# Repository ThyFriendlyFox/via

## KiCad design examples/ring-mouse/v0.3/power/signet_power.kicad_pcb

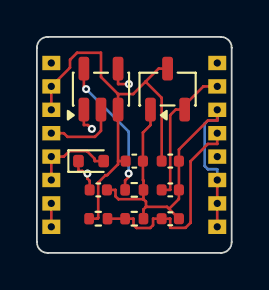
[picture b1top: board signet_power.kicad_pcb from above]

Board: 4 copper layers, 10.8 x 12.0 mm, 13 parts (0 on the bottom side), 8 nets.

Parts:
C1, C2: 4.7u; C_0402_1005Metric
C3, C4: 1u; C_0402_1005Metric
C5: 100n; C_0402_1005Metric
D2: BAT54XV2; D_SOD-523
J1: CELL; Joint_Edge_1x08_P1.3mm
J2: MOTION; Joint_Edge_1x08_P1.3mm
R1: 33k; R_0402_1005Metric
R2, R3: 1M; R_0402_1005Metric
U1: MCP73831; SOT-23-5
U2: TPS7A0533; SOT-23-3

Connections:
+3V3: C4.1, J2.2, U2.2
/CHG_STAT: J2.5, U1.1
/PROG: R1.1, U1.5
/VBAT_SENSE: C5.1, J2.4, R2.2, R3.1
GND: C1.2, C2.2, C3.2, C4.2, C5.2, J1.1, J1.4, J1.7, J1.8, J2.1, J2.3, J2.6, J2.7, J2.8, R1.2, R3.2, U1.2, U2.1
VBAT: C2.1, C3.1, J1.2, J1.3, R2.1, U1.3, U2.3
VCHG: D2.2, J1.5, J1.6
VIN_CHG: C1.1, D2.1, U1.4

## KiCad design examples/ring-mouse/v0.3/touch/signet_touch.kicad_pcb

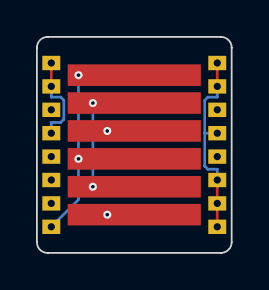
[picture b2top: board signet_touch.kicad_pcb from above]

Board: 4 copper layers, 10.8 x 12.0 mm, 3 parts (0 on the bottom side), 6 nets.

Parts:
E1: STRIP; TouchStrip_3ch_6x
J1: RADIO; Joint_Edge_1x08_P1.3mm
J2: CLICKS; Joint_Edge_1x08_P1.3mm

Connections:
/BTN_L: J1.5, J2.5
/BTN_R: J1.3, J2.3
/TOUCH_A: E1.1, J1.8
/TOUCH_B: E1.2, J1.7
/TOUCH_C: E1.3, J1.6
GND: J1.1, J1.2, J1.4, J2.1, J2.2, J2.4, J2.6, J2.7, J2.8

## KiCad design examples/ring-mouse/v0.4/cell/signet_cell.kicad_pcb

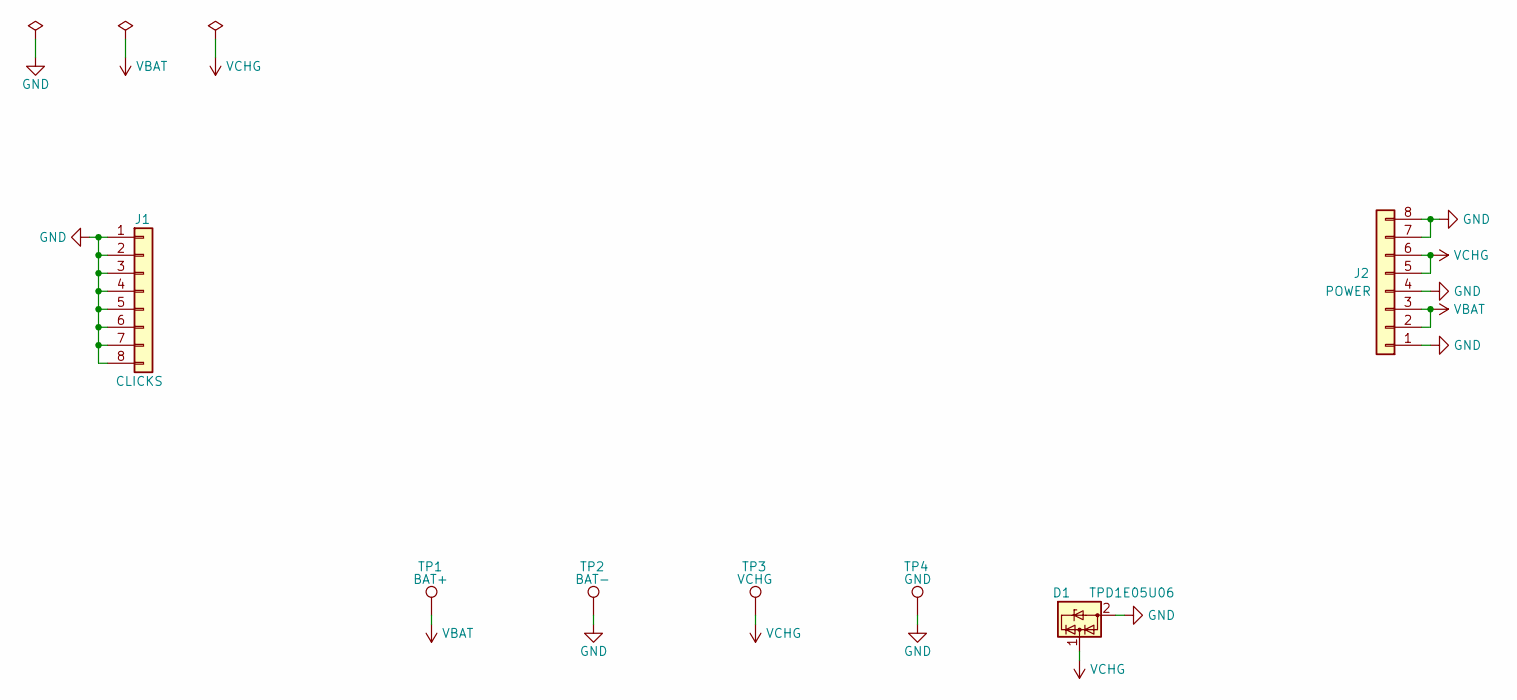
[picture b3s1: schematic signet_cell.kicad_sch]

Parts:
D1: TPD1E05U06; D_SOD-523
J1: CLICKS; Joint_Edge_1x08_P1.3mm
J2: POWER; Joint_Edge_1x08_P1.3mm
TP1: BAT+; TestPoint_Pad_1.5x1.5mm
TP2: BAT-; TestPoint_Pad_1.5x1.5mm
TP3: VCHG; TestPoint_Pad_D2.0mm
TP4: GND; TestPoint_Pad_D2.0mm

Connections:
GND: D1.2 (GND), J1.1, J1.2, J1.3, J1.4, J1.5, J1.6, J1.7, J1.8, J2.1, J2.4, J2.7, J2.8, TP2.1, TP4.1
VBAT: J2.2, J2.3, TP1.1
VCHG: D1.1 (I/O), J2.5, J2.6, TP3.1

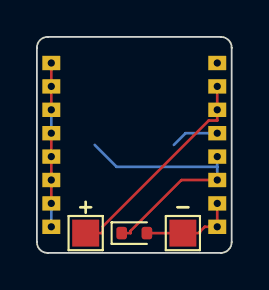
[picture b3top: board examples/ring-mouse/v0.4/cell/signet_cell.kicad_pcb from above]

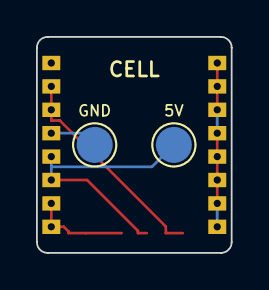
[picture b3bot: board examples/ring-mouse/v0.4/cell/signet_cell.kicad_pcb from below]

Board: 4 copper layers, 10.8 x 12.0 mm, 7 parts (2 on the bottom side), 3 nets.

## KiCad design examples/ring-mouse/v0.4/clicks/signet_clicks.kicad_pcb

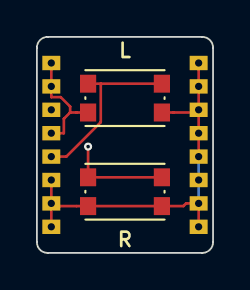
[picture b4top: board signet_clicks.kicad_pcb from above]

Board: 4 copper layers, 9.8 x 12.0 mm, 4 parts (0 on the bottom side), 3 nets.

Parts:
J1: TOUCH; Joint_Edge_1x08_P1.3mm
J2: CELL; Joint_Edge_1x08_P1.3mm
SW1: LEFT; SW_Push_1P1T_NO_CK_KMR2
SW2: RIGHT; SW_Push_1P1T_NO_CK_KMR2

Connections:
/BTN_L: J1.5, SW1.1
/BTN_R: J1.3, SW2.1
GND: J1.1, J1.2, J1.4, J1.6, J1.7, J1.8, J2.1, J2.2, J2.3, J2.4, J2.5, J2.6, J2.7, J2.8, SW1.2, SW2.2

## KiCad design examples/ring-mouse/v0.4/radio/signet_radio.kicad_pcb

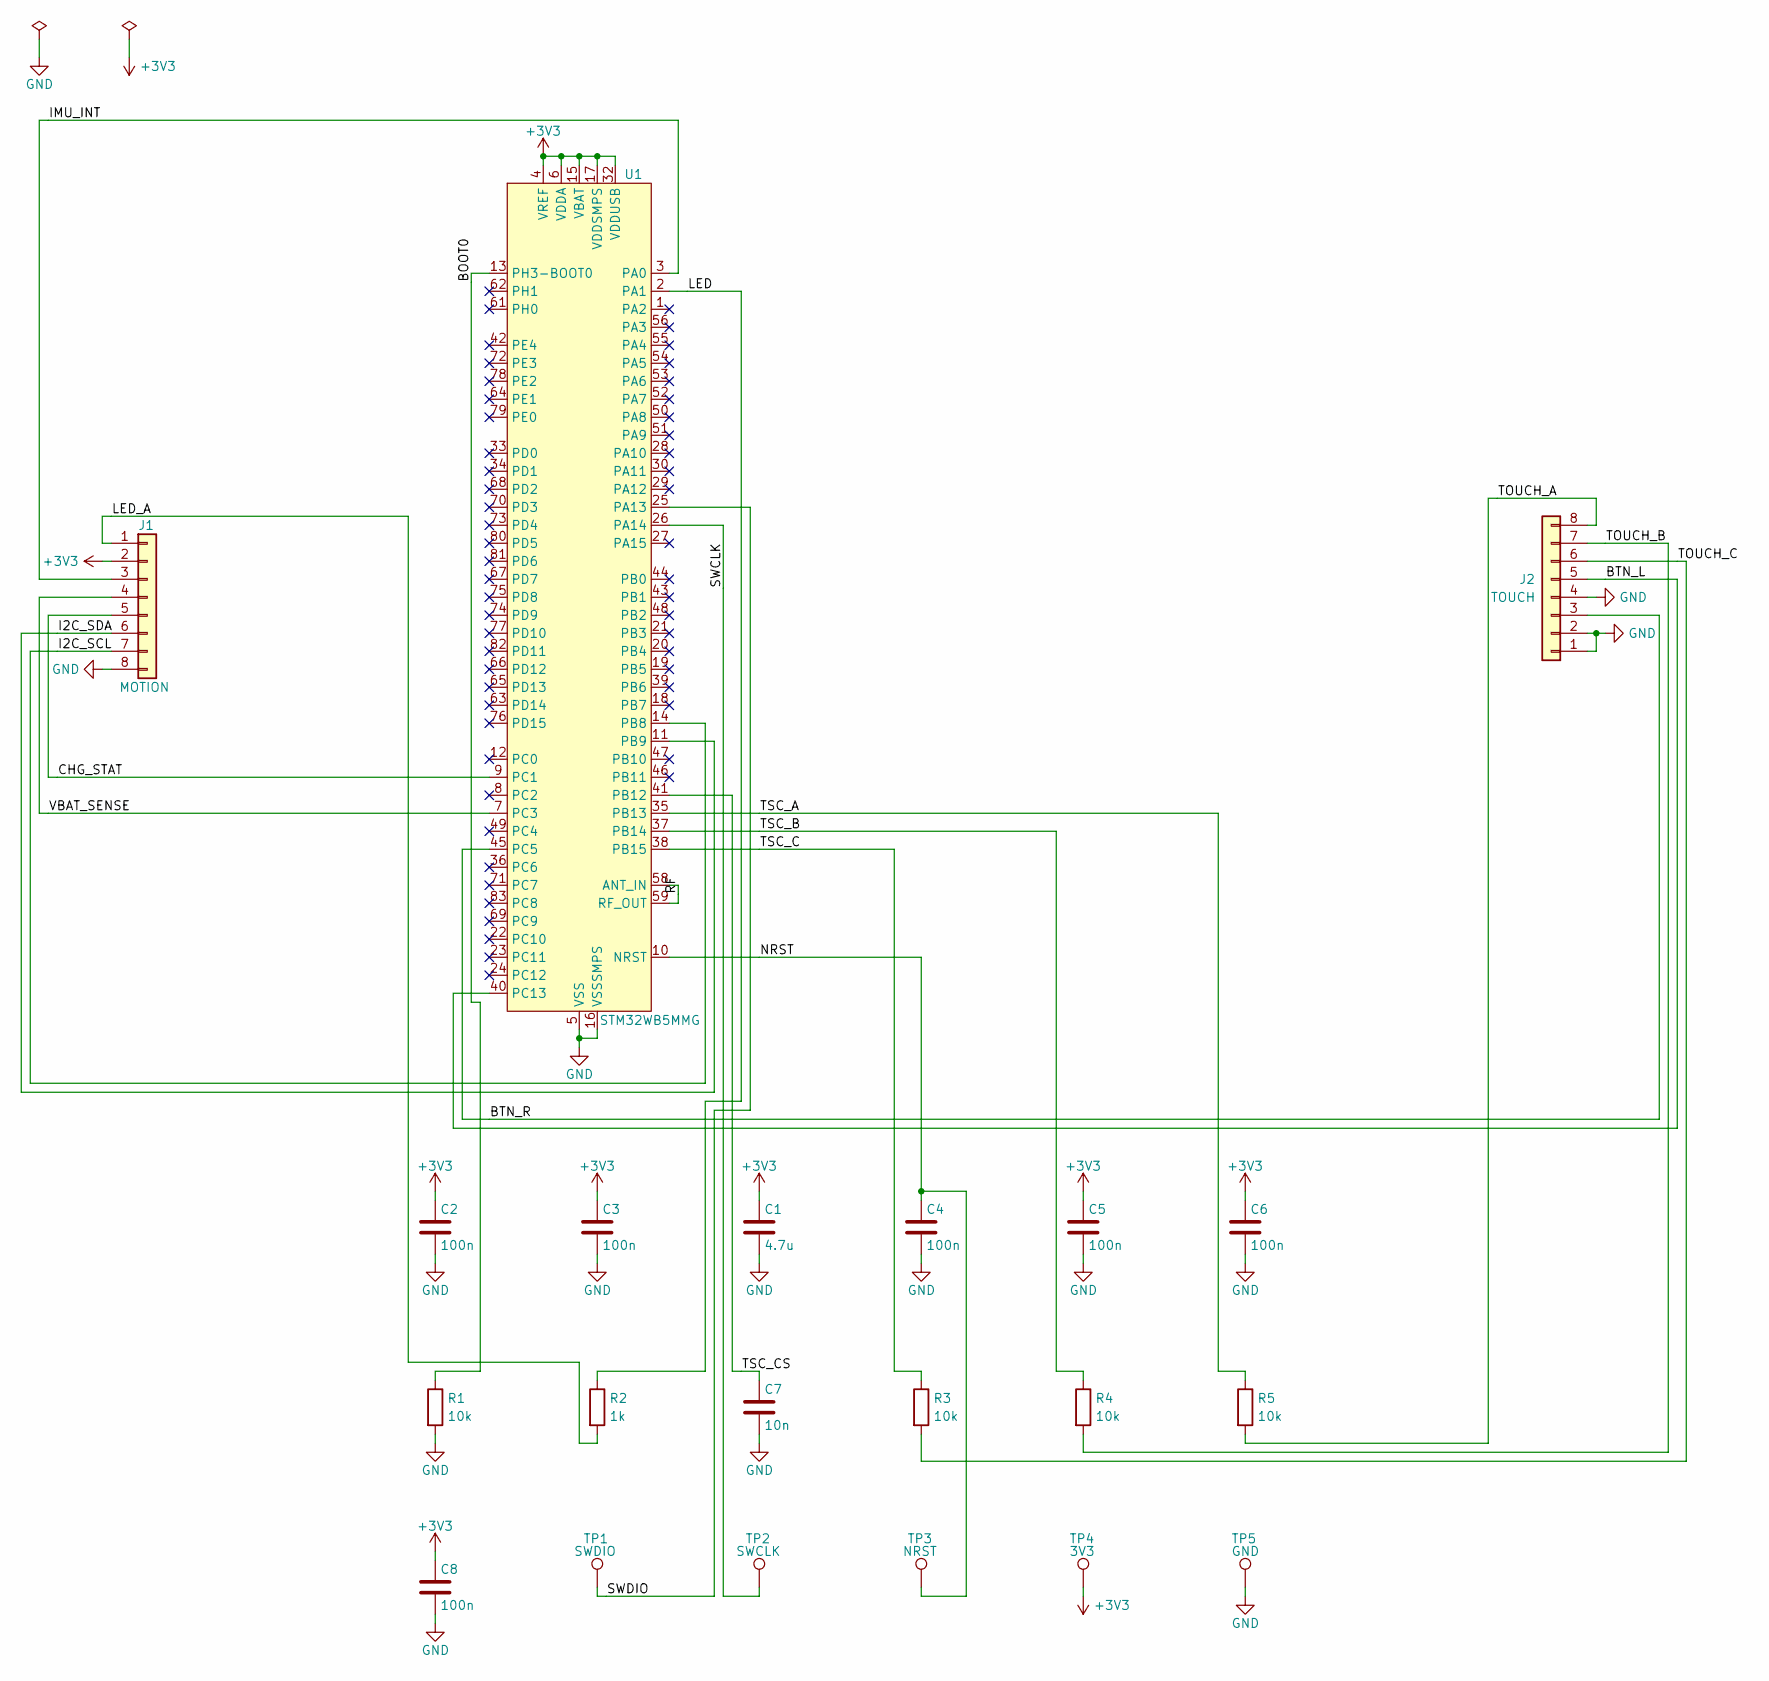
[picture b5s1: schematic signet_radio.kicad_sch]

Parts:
C1: 4.7u; C_0402_1005Metric
C2, C3, C4, C5, C6, C8: 100n; C_0402_1005Metric
C7: 10n; C_0402_1005Metric
J1: MOTION; Joint_Edge_1x08_P1.3mm
J2: TOUCH; Joint_Edge_1x08_P1.3mm
R1, R3, R4, R5: 10k; R_0402_1005Metric
R2: 1k; R_0402_1005Metric
TP1: SWDIO; TestPoint_Pad_D1.0mm
TP2: SWCLK; TestPoint_Pad_D1.0mm
TP3: NRST; TestPoint_Pad_D1.0mm
TP4: 3V3; TestPoint_Pad_D1.0mm
TP5: GND; TestPoint_Pad_D1.0mm
U1: STM32WB5MMG; ST-SiP-LGA-86-11x7.3mm

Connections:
+3V3: C1.1, C2.1, C3.1, C5.1, C6.1, C8.1, J1.2, TP4.1, U1.4 (VREF), U1.6 (VDDA), U1.15 (VBAT), U1.17 (VDDSMPS), U1.32 (VDDUSB)
/BOOT0: R1.1, U1.13 (PH3-BOOT0)
/BTN_L: J2.5, U1.40 (PC13)
/BTN_R: J2.3, U1.45 (PC5)
/CHG_STAT: J1.5, U1.9 (PC1)
/I2C_SCL: J1.7, U1.14 (PB8)
/I2C_SDA: J1.6, U1.11 (PB9)
/IMU_INT: J1.3, U1.3 (PA0)
/LED: R2.1, U1.2 (PA1)
/LED_A: J1.1, R2.2
/NRST: C4.1, TP3.1, U1.10 (NRST)
/RF: U1.58 (ANT_IN), U1.59 (RF_OUT)
/SWCLK: TP2.1, U1.26 (PA14)
/SWDIO: TP1.1, U1.25 (PA13)
/TOUCH_A: J2.8, R5.2
/TOUCH_B: J2.7, R4.2
/TOUCH_C: J2.6, R3.2
/TSC_A: R5.1, U1.35 (PB13)
/TSC_B: R4.1, U1.37 (PB14)
/TSC_C: R3.1, U1.38 (PB15)
/TSC_CS: C7.1, U1.41 (PB12)
/VBAT_SENSE: J1.4, U1.7 (PC3)
GND: C1.2, C2.2, C3.2, C4.2, C5.2, C6.2, C7.2, C8.2, J1.8, J2.1, J2.2, J2.4, R1.2, TP5.1, U1.5 (VSS), U1.16 (VSSSMPS), U1.31 (VSS), U1.57 (VSS), U1.60 (VSS), U1.84 (VSS), U1.86 (VSS)

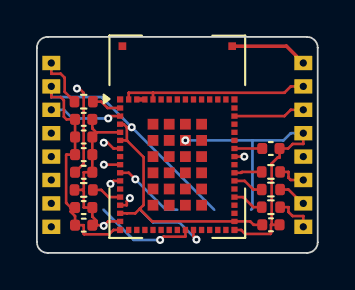
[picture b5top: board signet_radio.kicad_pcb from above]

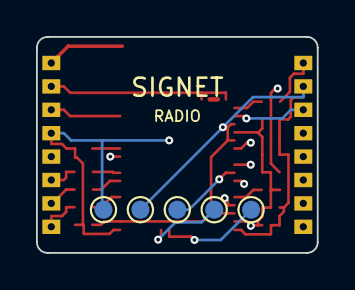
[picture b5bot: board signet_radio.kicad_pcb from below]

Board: 4 copper layers, 15.6 x 12.0 mm, 21 parts (5 on the bottom side), 23 nets.

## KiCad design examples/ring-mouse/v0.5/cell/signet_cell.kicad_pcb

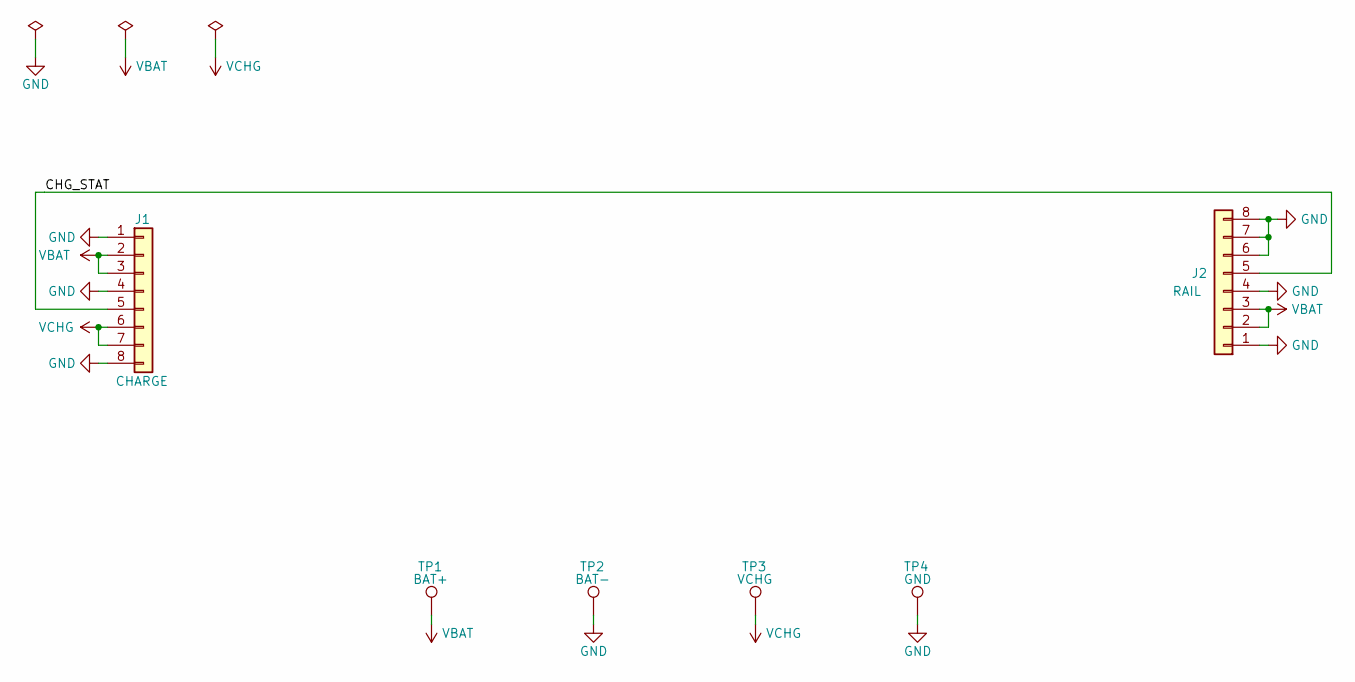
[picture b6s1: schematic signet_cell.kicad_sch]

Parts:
J1: CHARGE; Joint_Edge_1x08_P1.3mm
J2: RAIL; Joint_Edge_1x08_P1.3mm
TP1: BAT+; CellTab_1x1.4mm
TP2: BAT-; CellTab_1x1.4mm
TP3: VCHG; TestPoint_Pad_D1.0mm
TP4: GND; TestPoint_Pad_D1.0mm

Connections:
/CHG_STAT: J1.5, J2.5
GND: J1.1, J1.4, J1.8, J2.1, J2.4, J2.6, J2.7, J2.8, TP2.1, TP4.1
VBAT: J1.2, J1.3, J2.2, J2.3, TP1.1
VCHG: J1.6, J1.7, TP3.1

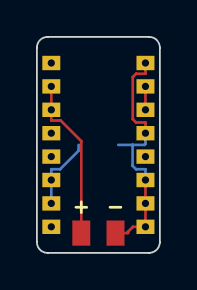
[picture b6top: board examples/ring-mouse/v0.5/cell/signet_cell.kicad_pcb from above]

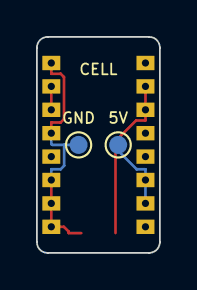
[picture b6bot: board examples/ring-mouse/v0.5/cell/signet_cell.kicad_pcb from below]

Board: 4 copper layers, 6.8 x 12.0 mm, 6 parts (2 on the bottom side), 4 nets.
